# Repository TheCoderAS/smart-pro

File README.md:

# Unisync — Marketing Site

A dark, deliberately quiet marketing site for Unisync, a pre-launch smart-switch
company in Bangalore. Built per `docs/Website_Build_Brief_for_Agent.md` (the
visual / IA brief) and amended per Unisync's change request: rebrand to Unisync,
new Product section explaining the master + extension + mesh architecture, inline
waitlist form replacing the modal, contact email rewires, and the team section
removed until founder names are public.

Stack: Next.js 14 (App Router) + TypeScript + Tailwind CSS + Framer Motion.

## Setup

```bash
pnpm install
pnpm dev
```

The site runs at <http://localhost:3000>.

Other scripts:

```bash
pnpm build    # production build (also runs typechecking)
pnpm start    # serve the production build
pnpm lint     # next lint
```

## Page composition

```
/  (single-page narrative, scrolls top to bottom)
   Hero
   01 — The problem
   02 — The product           (architecture diagram + sub-bullets)
   03 — Our approach           (4 pillars: Networked / Local / Open / Installers)
   04 — Built for              (Homeowners / Electricians / Builders)
   Waitlist                    (id="waitlist", inline form + reach-us-directly)

/installers  — electrician-facing landing page
/press       — press kit
/privacy     — privacy boilerplate (TODO: legal review)
/terms       — terms boilerplate (TODO: legal review)
```

## Project structure

```
app/
├── layout.tsx                 # Root layout: fonts, nav, footer, motion config, SEO
├── page.tsx                   # Main page composition
├── installers/                # Sub-route
├── press/                     # Sub-route
├── privacy/                   # Sub-route (legal placeholder)
├── terms/                     # Sub-route (legal placeholder)
├── api/waitlist/              # Stubbed waitlist endpoint
├── api/installer-interest/    # Stubbed installer-interest endpoint
└── globals.css                # CSS variables, base styles, grain, gridlines
components/
├── layout/                    # Nav, Footer, ScrollProgress, ReducedMotionProvider
├── sections/                  # Hero, Problem, Product, Approach, Audiences, Waitlist
├── ui/                        # Button, EyebrowLabel, RevealText, SectionNumber
└── illustrations/             # HeroSchematic + ArchitectureDiagram (Product section)
lib/
├── motion.ts                  # Shared Framer Motion variants and easings
└── utils.ts                   # cn() helper
```

## Placeholders to replace before launch

Search the codebase (`grep -r "TODO" .`) and replace each of the following before going public:

- **`unisync.in` domain** — assumed-available throughout. If `.in` turns out
  to be unavailable when the domain is registered, fall back to `getunisync.in`
  or `unisync.app` and find/replace globally. Currently set in `app/layout.tsx`
  (`metadataBase`, canonical, `og:url`).
- **`aalokmamtasah@gmail.com`** — currently the single contact address
  everywhere. Replace with dedicated mailboxes (`hello@`, `investors@`,
  `press@`, `careers@`, `builders@`) once the domain is live and inboxes
  are set up. Search-and-replace, then split per intent. Subject prefixes
  (`?subject=Investors`, `?subject=Press`, etc.) on the "Or reach us
  directly" block let visitors self-identify in the meantime.
- **`/public/og-image.jpg`** — 1200×630 Open Graph / Twitter card image.
  Brief: off-white background, centred Unisync wordmark in navy, tagline
  ("The wall should be smarter than the bulb.") below in muted type, a soft
  product photo cropped to the right third.
- **Brand assets** linked from `/press` — replace the placeholder
  `wordmark.svg` at `public/brand/wordmark.svg` with the real wordmark
  (and add `wordmark.png` and `wordmark.pdf` so the "Coming soon" rows
  flip to live downloads).
- **Founders / team** — currently omitted from the homepage entirely. The
  `/press` page still uses `[Founder Name]` / `[Role]` placeholders for
  the founder cards; replace once names are public.
- **Legal copy** in `app/privacy/page.tsx` and `app/terms/page.tsx`
  (marked `// TODO: replace with content reviewed by counsel`).
- **Social URLs** in `components/layout/Footer.tsx` — currently
  `https://instagram.com/unisync.in`, `https://youtube.com/@unisync`,
  `https://linkedin.com/company/unisync` (placeholders; the `@unisync`
  handle on Instagram/X is squatted, so confirm what's actually
  reachable).
- **`/api/waitlist`** — currently logs `{ email, city, role }` to the
  server console and returns `{ ok: true }`. Wire up to a real backend
  (Resend, Loops, Airtable, Tally, Google Forms — whichever is fastest).
- **`/api/installer-interest`** — same shape, same TODO.
- **Cookie consent banner** — explicitly out of scope; evaluate before
  public launch.

## Deployment (Vercel)

Push the repo to GitHub and import it in the Vercel dashboard. Vercel
auto-detects Next.js — no config required. Set the production domain
(`unisync.in`), point DNS, and add any environment variables once the
waitlist and installer-interest endpoints are wired to a real backend.
Each push to the configured production branch triggers a deploy.

## Design notes

This site is intentionally quiet. The aesthetic is "late-night editorial
meets industrial precision": dark background, warm off-white type,
generous negative space, one warm-copper accent (`#D97757`) used like
punctuation — never on body text, never as a large fill. If you find
yourself wanting to add a second colour, a hero photo, a "Trusted by"
logo row, or a punchier "Get Started" button, stop. The discipline is the
point.

Animations are slow and decelerating (a single shared cubic-bezier
`(0.22, 1, 0.36, 1)`); nothing wobbles or bounces. New decorative
elements should be inline SVG built from straight lines and small
circles, in the spirit of `HeroSchematic` and `ArchitectureDiagram`.
The accent should appear on roughly 5–7 elements when the whole page is
scrolled — count before adding more.

CSS color tokens are defined in two forms in `app/globals.css`:
the hex form (`--accent`) for direct CSS use (e.g. `fill="var(--accent)"`)
and the rgb-channels form (`--accent-rgb`) consumed by Tailwind via
`rgb(var(--x-rgb) / <alpha-value>)` so opacity modifiers (`bg-bg/70`,
`text-fg-faint/20`) work correctly. Don't drop one form thinking it's
unused — both are needed.

Fonts are pinned: **Fraunces** (display), **Geist Sans** (body),
**JetBrains Mono** (eyebrows / labels). Do not substitute Inter, Roboto,
or Space Grotesk.

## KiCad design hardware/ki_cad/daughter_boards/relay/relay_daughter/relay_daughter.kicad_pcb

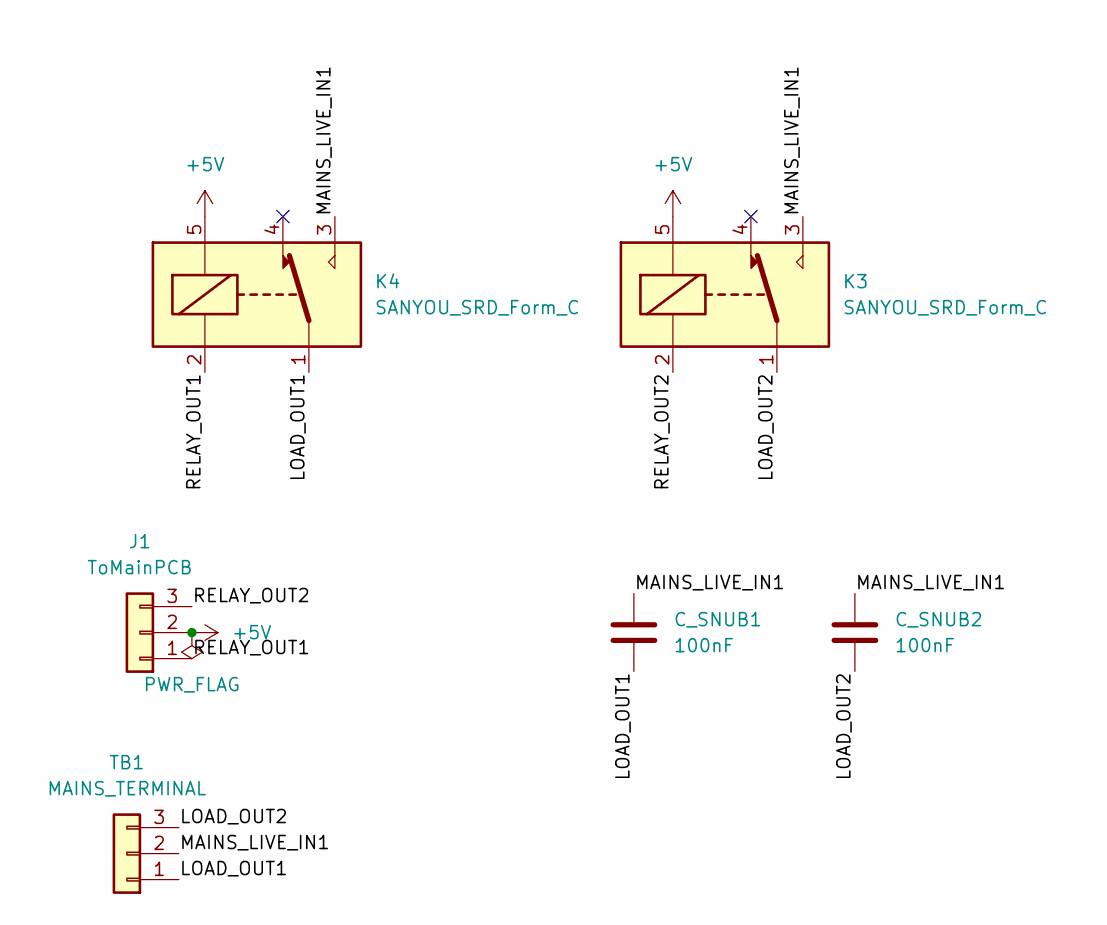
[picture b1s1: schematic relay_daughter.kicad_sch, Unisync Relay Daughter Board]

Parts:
C_SNUB1, C_SNUB2: 100nF; C_Rect_L18.0mm_W5.0mm_P15.00mm_FKS3_FKP3
J1: ToMainPCB; PinHeader_1x03_P2.54mm_Vertical
K3, K4: SANYOU_SRD_Form_C; Relay_SPDT_SANYOU_SRD_Series_Form_C
TB1: MAINS_TERMINAL; TerminalBlock_RND_205-00046_1x03_P5.00mm_Horizontal

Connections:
+5V: J1.2, K3.5, K4.5
/LOAD_OUT1: C_SNUB1.2, K4.1, TB1.1
/LOAD_OUT2: C_SNUB2.2, K3.1, TB1.3
/MAINS_LIVE_IN1: C_SNUB1.1, C_SNUB2.1, K3.3, K4.3, TB1.2
/RELAY_OUT1: J1.1, K4.2
/RELAY_OUT2: J1.3, K3.2

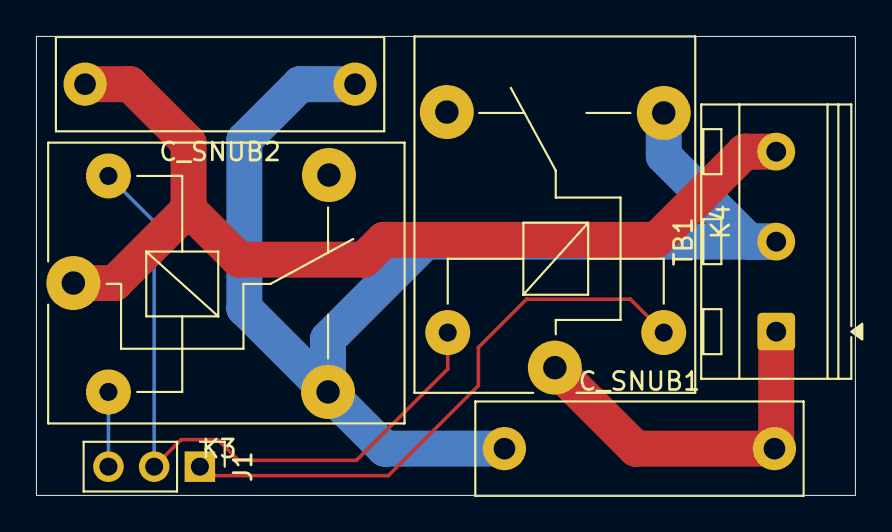
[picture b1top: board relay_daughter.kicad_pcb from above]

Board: 2 copper layers, 45.5 x 25.5 mm, 7 parts (1 on the bottom side), 6 nets.

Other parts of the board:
logo1: LOGO; Unisync_15mm

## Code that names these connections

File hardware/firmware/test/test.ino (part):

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#define PIN_READ(pin)   ((GPIOA->IDR  >> (pin)) & 1u)

/* Pin numbers (bit positions in GPIOA) */
#define PIN_RS485_DE   0
#define PIN_RELAY1     1
#define PIN_RELAY2     2
#define PIN_TOUCH1     3
#define PIN_TOUCH2     4
#define PIN_LED1       5
#define PIN_LED2       6
#define PIN_LED3       7
/* PA9=TX, PA10=RX handled by USART1 alternate function */

/* ================================================================
 * PROTOCOL
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    RCC->IOPENR  |= RCC_IOPENR_GPIOAEN;
    /* SYSCFG remap -- required for USART1 on G030 */
    SYSCFG->CFGR1 |= SYSCFG_CFGR1_PA11_RMP | SYSCFG_CFGR1_PA12_RMP;
    /* PA9 = AF1 TX: high speed, push-pull */
    GPIOA->MODER   = (GPIOA->MODER   & ~(3u<<18)) | (2u<<18);
    GPIOA->AFR[1]  = (GPIOA->AFR[1]  & ~(15u<<4)) | (1u<<4);
    GPIOA->OSPEEDR = (GPIOA->OSPEEDR & ~(3u<<18)) | (3u<<18);
    GPIOA->OTYPER &= ~(1u<<9);
    /* PA10 = AF1 RX: pull-up */
    GPIOA->MODER  = (GPIOA->MODER  & ~(3u<<20)) | (2u<<20);
    GPIOA->AFR[1] = (GPIOA->AFR[1] & ~(15u<<8)) | (1u<<8);
    GPIOA->PUPDR  = (GPIOA->PUPDR  & ~(3u<<20)) | (1u<<20);
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    /* Relay HIGH before output (active LOW = OFF) */
    GPIOA->BSRR = (1u<<1)|(1u<<2);
    GPIOA->BRR  = (1u<<0)|(1u<<5)|(1u<<6)|(1u<<7);
    /* PA0,1,2,5,6,7=output PA3,4=input no-pull */
    GPIOA->MODER = (GPIOA->MODER
        & ~((3u<<0)|(3u<<2)|(3u<<4)|(3u<<6)|(3u<<8)|(3u<<10)|(3u<<12)|(3u<<14)))
        |  ((1u<<0)|(1u<<2)|(1u<<4)|(1u<<10)|(1u<<12)|(1u<<14));
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static uint32_t announce_interval = 2000;

/* ================================================================
 * BREATH TICK -- TIM17 hardware PWM on PA7
 * Registered: 32 * 125ms = 4s cycle
 * Unregistered: 32 * 31ms = ~1s cycle
 * ================================================================ */
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
static void tim17_pwm_init(void) {
    RCC->APBENR2 |= RCC_APBENR2_TIM17EN;
    /* PA7 = AF5 (TIM17_CH1) push-pull */
    GPIOA->MODER  = (GPIOA->MODER  & ~(3u<<14)) | (2u<<14);
    GPIOA->AFR[0] = (GPIOA->AFR[0] & ~(15u<<28)) | (5u<<28);
    TIM17->PSC   = 0;
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 * RS-485 TRANSPORT
 * ================================================================ */
static void rs485_send(uint8_t *frame, uint8_t len) {
    PIN_SET(PIN_RS485_DE);
    __NOP(); __NOP(); __NOP(); __NOP(); /* ~250ns guard */
    for (uint8_t i = 0; i < len; i++) usart1_write_byte(frame[i]);
    usart1_wait_tc();
    __NOP(); __NOP(); __NOP(); __NOP();
    PIN_CLR(PIN_RS485_DE);
    /* MAX3485 RX enable guard + flush echo bytes */
    __NOP(); __NOP(); __NOP(); __NOP();
    if (USART1->ISR & USART_ISR_ORE) USART1->ICR = USART_ICR_ORECF;
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 * ================================================================ */
static void set_relay1(bool s) {
    relay1_state = s;
    if (s) { PIN_CLR(PIN_RELAY1); PIN_SET(PIN_LED1); }
    else   { PIN_SET(PIN_RELAY1); PIN_CLR(PIN_LED1); }
}

static void set_relay2(bool s) {
    relay2_state = s;
    if (s) { PIN_CLR(PIN_RELAY2); PIN_SET(PIN_LED2); }
    else   { PIN_SET(PIN_RELAY2); PIN_CLR(PIN_LED2); }
}

/* ================================================================
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
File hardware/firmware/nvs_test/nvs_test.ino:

/*
 * Relay + LED State Restore Test -- STM32G030F6P6
 * Touch PA3 toggles RELAY1+LED1
 * Touch PA4 toggles RELAY2+LED2
 * Both states persist across power cycles.
 *
 * PA3 = TOUCH1  (input)
 * PA4 = TOUCH2  (input)
 * PA1 = RELAY1  (active LOW -- LOW=ON, HIGH=OFF)
 * PA2 = RELAY2  (active LOW -- LOW=ON, HIGH=OFF)
 * PA5 = LED1    (active HIGH -- HIGH=ON, LOW=OFF)
 * PA6 = LED2    (active HIGH -- HIGH=ON, LOW=OFF)
 */

#include "Arduino.h"
#include <stm32g0xx_ll_gpio.h>
#include <stm32g0xx_ll_bus.h>

#define PIN_T1     3
#define PIN_T2     4
#define PIN_RELAY1 1
#define PIN_RELAY2 2
#define PIN_LED1   5
#define PIN_LED2   6
#define PIN_SET(p) (GPIOA->BSRR = (1u<<(p)))
#define PIN_CLR(p) (GPIOA->BRR  = (1u<<(p)))
#define PIN_READ(p)((GPIOA->IDR  >>(p))&1u)

#define NVS_PAGE_ADDR  0x08007800UL
#define NVS_MAGIC_VAL  0xA5

static uint8_t shadow[8];

static void nvs_load(void) {
    volatile uint8_t *p = (volatile uint8_t *)NVS_PAGE_ADDR;
    for (int i = 0; i < 8; i++) shadow[i] = p[i];
}

static void nvs_flush(void) {
    if (READ_BIT(FLASH->CR, FLASH_CR_LOCK)) {
        WRITE_REG(FLASH->KEYR, 0x45670123UL);
        WRITE_REG(FLASH->KEYR, 0xCDEF89ABUL);
    }
    WRITE_REG(FLASH->SR, 0xFFFFFFFF);
    MODIFY_REG(FLASH->CR, FLASH_CR_PNB, (15u << FLASH_CR_PNB_Pos));
    SET_BIT(FLASH->CR, FLASH_CR_PER);
    SET_BIT(FLASH->CR, FLASH_CR_STRT);
    uint32_t t = millis();
    while (READ_BIT(FLASH->SR, FLASH_SR_BSY1) && (millis()-t) < 500);
    CLEAR_BIT(FLASH->CR, FLASH_CR_PER);
    WRITE_REG(FLASH->SR, FLASH_SR_EOP);
    SET_BIT(FLASH->CR, FLASH_CR_PG);
    volatile uint32_t *dst = (volatile uint32_t *)NVS_PAGE_ADDR;
    uint32_t w0, w1;
    memcpy(&w0, &shadow[0], 4);
    memcpy(&w1, &shadow[4], 4);
    dst[0] = w0; __ISB(); dst[1] = w1;
    t = millis();
    while (READ_BIT(FLASH->SR, FLASH_SR_BSY1) && (millis()-t) < 500);
    CLEAR_BIT(FLASH->CR, FLASH_CR_PG);
    WRITE_REG(FLASH->SR, FLASH_SR_EOP);
    SET_BIT(FLASH->CR, FLASH_CR_LOCK);
}

static bool r1 = false;
static bool r2 = false;

static void set_relay1(bool s) {
    r1 = s;
    if (s) { PIN_CLR(PIN_RELAY1); PIN_SET(PIN_LED1); }  /* ON */
    else   { PIN_SET(PIN_RELAY1); PIN_CLR(PIN_LED1); }  /* OFF */
}

static void set_relay2(bool s) {
    r2 = s;
    if (s) { PIN_CLR(PIN_RELAY2); PIN_SET(PIN_LED2); }  /* ON */
    else   { PIN_SET(PIN_RELAY2); PIN_CLR(PIN_LED2); }  /* OFF */
}

static void save(void) {
    shadow[0] = NVS_MAGIC_VAL;
    shadow[1] = (r1 ? 0x01 : 0x00) | (r2 ? 0x02 : 0x00);
    nvs_flush();
}

void setup() {
    LL_IOP_GRP1_EnableClock(LL_IOP_GRP1_PERIPH_GPIOA);

    /* Set relay pins HIGH before output mode (active LOW = OFF) */
    GPIOA->BSRR = LL_GPIO_PIN_1 | LL_GPIO_PIN_2;

    LL_GPIO_SetPinMode(GPIOA, LL_GPIO_PIN_1, LL_GPIO_MODE_OUTPUT);
    LL_GPIO_SetPinMode(GPIOA, LL_GPIO_PIN_2, LL_GPIO_MODE_OUTPUT);
    LL_GPIO_SetPinMode(GPIOA, LL_GPIO_PIN_5, LL_GPIO_MODE_OUTPUT);
    LL_GPIO_SetPinMode(GPIOA, LL_GPIO_PIN_6, LL_GPIO_MODE_OUTPUT);
    LL_GPIO_SetPinMode(GPIOA, LL_GPIO_PIN_3, LL_GPIO_MODE_INPUT);
    LL_GPIO_SetPinMode(GPIOA, LL_GPIO_PIN_4, LL_GPIO_MODE_INPUT);
    LL_GPIO_SetPinPull(GPIOA, LL_GPIO_PIN_3, LL_GPIO_PULL_NO);
    LL_GPIO_SetPinPull(GPIOA, LL_GPIO_PIN_4, LL_GPIO_PULL_NO);
    PIN_CLR(PIN_LED1);
    PIN_CLR(PIN_LED2);

    nvs_load();
    if (shadow[0] == NVS_MAGIC_VAL) {
        set_relay1((shadow[1] & 0x01) != 0);
        set_relay2((shadow[1] & 0x02) != 0);
    }
}

void loop() {
    static bool last1 = false;
    static bool last2 = false;
    bool t1 = PIN_READ(PIN_T1);
    bool t2 = PIN_READ(PIN_T2);
    if (t1 && !last1) { set_relay1(!r1); save(); }
    if (t2 && !last2) { set_relay2(!r2); save(); }
    last1 = t1;
    last2 = t2;
}

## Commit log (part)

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2026-05-13 Init
2026-05-13 Add pre-MVP marketing site per build brief
    Implements the dark, stealth-ish single-page site described in
    docs/Website_Build_Brief_for_Agent.md: hero + problem + approach +
    audiences + team sections, three sub-routes (installers, press,
    privacy/terms), and stubbed waitlist + installer-interest API routes.
    - Next.js 14 App Router + TypeScript + Tailwind + Framer Motion
    - Fraunces / Geist Sans / JetBrains Mono fonts via next/font
2026-05-13 Fix small post-build loose ends
    - Drop dead /#faq link in Footer; repoint Resources column to Early
    access / Investors / Press.
    - Add placeholder wordmark.svg under public/brand/; press page now
    only renders a live link for the SVG and shows the PNG/PDF rows as
    "Coming soon" so nothing 404s.
    - Make press founder bios obvious placeholders so they're easy to grep
2026-05-13 Fix mobile responsiveness — text overflow and section number intrusion
    Reported on the Vercel preview: text overlapping and overflowing the
    viewport on small screens. Three causes, three fixes:
    1. Type scale mins were too aggressive for a 375px viewport. At 40px
    (the previous text-h1 floor) the word "infrastructure" was wider
    than the available content area. Lowered:
    - text-hero 3.5rem → 2.5rem min
2026-05-13 Fix opacity modifiers + bring section numbers inside the viewport
    Real root cause of the "overlapping" report on mobile (screenshot
    showed a nearly-white giant '0' bleeding into body text):
    Tailwind /<alpha> opacity modifiers were silently no-oping on every
    custom colour. The CSS variables were defined as hex strings, but
    Tailwind only honours the slash-opacity syntax when the colour token
    uses the `rgb(... / <alpha-value>)` pattern. So `text-fg-faint/30` on
2026-05-14 Apply Unisync change request — rebrand, Product section, inline waitlist
    Implements docs/Unisync_Website_Change_Request.md (delivered out-of-tree).
    Brand fill-in
    - [BRAND] → Unisync, [CITY] → Bangalore, brand.com → unisync.in across
    copy, metadata, og tags, canonical URL, and the placeholder wordmark.
    - All mailto links repointed to aalokmamtasah@gmail.com (with ?subject=
    prefilled on the contact block so visitors can self-identify).
2026-05-14 Add brochure download link (Hero secondary CTA + Footer)
    Pulled docs/Smart_Switch_Pitch_v1.pdf (the pitch deck added to main)
    into public/ so Next.js serves it as a same-origin static file. Clicks
    trigger a browser download instead of routing to GitHub.
    - Hero gets a third secondary CTA "Download brochure ↓" alongside the
    existing "For investors →" mailto. Both are subtle text links so the
    primary "Request early access" button stays the visual anchor.
2026-05-14 Replay scroll-triggered animations each time a section re-enters viewport
    Currently every whileInView reveal fires once and then stays put — the
    shared `VIEWPORT_ONCE` viewport config used `once: true`, matching the
    original brief's intent. The user wants reveals to replay when a section
    is scrolled back into view.
    Renamed `VIEWPORT_ONCE` → `VIEWPORT_REPEAT` (so the name reflects the
    new behaviour) and flipped `once: true` → `once: false`. The 100px
2026-05-14 Add ambient connected-nodes mesh behind the hero
    Lightweight canvas mesh that drifts slowly behind hero content. Reads
    as live drafting paper rather than the usual particles.js "tech
    startup" cliche by:
    - Using fg-muted (not accent) for both lines and nodes, so it doesn't
    burn the accent budget. Lines fade with distance.
    - Limiting to ~35 nodes with a 160 px connection threshold, slow drift.
2026-05-14 Rewrite NodesBackground: full-page mesh + cursor-tethered main node
    User wants the mesh to demonstrate the product behaviour — a single
    main node sticks to the pointer and propagates messages out to the
    nearest peers — and to span the whole page, not just the hero.
    Changes from the previous quiet-hero-mesh draft:
    - Mount moved from Hero.tsx to app/layout.tsx, behind every route.
    - Canvas is `position: fixed` to the viewport, z-index: 0 so it sits
2026-05-14 Brighten mesh, add cursor↔main link, guarantee one connection per node
    Three fixes against the previous attempt:
    1) Mesh was barely visible. Bumped:
    - Non-main line alpha multiplier 0.14 → 0.40
    - Main line alpha multiplier 0.55 → 0.70
    - Node fill alpha 0.55 → 0.85
    - Density 55 → 60 nodes
2026-05-14 Static nodes, max 8 peer edges per node, +1 cursor link
    Three behaviour changes:
    1) Nodes are now static. Placed once at mount via stratified-random
    sampling (one node per grid cell with jitter) for even visual
    coverage. On window resize their positions scale proportionally so
    the mesh pattern is preserved.
    2) Edge construction is deterministic and capped:
2026-05-14 Raise mesh edge alpha floor so long edges stay readable
    Previously edge alpha = (1 - d/CONNECT_DISTANCE) * k, which trended to
    zero near the connection threshold — edges close to the cap distance
    were barely visible.
    Now a brightness floor + smaller gradient:
    peer edges: 0.35 → 0.60 (floor + near/far cue)
    main edges: 0.55 → 0.90
2026-05-14 Restore slow drift — DRIFT = 0.08, edges rebuilt each frame
    Fully static layout felt too flat. Re-introducing gentle ambient
    motion at less than half the previously-shipped speed.
    DRIFT = 0.08 (vs 0.20 in the merged PR #8 drifting version)
    Implementation notes:
    - Nodes drift and bounce off viewport edges (as before).
    - The edge graph is rebuilt every frame so the MAX_DEGREE=8 cap stays
2026-05-14 Enforce min-distance 150 between nodes, planar drift only
    Two changes:
    1) Minimum-distance constraint between nodes (150 px).
    - Seed placement now uses Poisson-disc rejection sampling: each
    candidate position is accepted only if it's ≥ MIN_DISTANCE from
    every already-placed node. Eliminates clumping at mount.
    - Per-frame repulsion: any pair closer than MIN_DISTANCE during
2026-05-14 Remove Hero schematic + Architecture diagram, footer to solid black
    Three small UI changes:
    1) Footer background → bg-black. The page bg is #0a0a0b (slight blue
    tint); the footer is now true #000 so it reads as a distinct dark
    slab beneath the main content. Footer is already at z-index 2 per
    globals.css so it sits above the NodesBackground canvas.
    2) Removed <HeroSchematic /> from the Hero section. The drifting mesh
2026-05-14 Mesh: 150 px min-distance with auto-scaling spacing (not count)
    The mesh now enforces a minimum distance between nodes while keeping
    all NODE_COUNT (60) nodes on every viewport. The spacing is what
    flexes for small screens, not the node count.
    Why: dropping nodes on small viewports changed the visual story
    (sparse vs dense mesh on phone vs desktop). Shrinking the gap instead
    keeps the same density on every device — only the absolute pixel gap
2026-06-08 bare minimum
2026-06-08 extension without ISR
2026-06-09 master v1
2026-06-14 working versions
2026-06-14 preserve state acoss restarts
2026-06-14 Fixes
2026-06-16 new architecture design
2026-06-16 new architecture fixes
2026-06-17 master OTA
2026-06-17 pin updated
2026-06-17 timing fixes
2026-06-18 v6.1 — touch relay active LOW fix
